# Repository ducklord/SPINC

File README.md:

# SPINC - DIY Automatic Battery Charger

## Overview

SPINC is an Open-Source NiMH charging station that can automatically load and eject AA battery cells. Simply drop batteries into the top of the device, regardless of their polarity. The internal mechanism picks up one cell at a time and fast-charges them sequentially. Up to 7 fully charged batteries can be conveniently stored inside the device for easy access. In addition, SPINC doubles as a desk clock, displaying the date and time on its high-resolution LCD.

<div align="center">
  
</div>

### Features
* Fast-charges AA NiMH cells at up to 1A
* Automatic cell loading and ejection
* Electronic polarity-correction
* Voltage, temperature and charge time monitoring
* 240x400px monochrome LCD
* Date and time display using LVGL interface
* Compact and fully 3D-printed

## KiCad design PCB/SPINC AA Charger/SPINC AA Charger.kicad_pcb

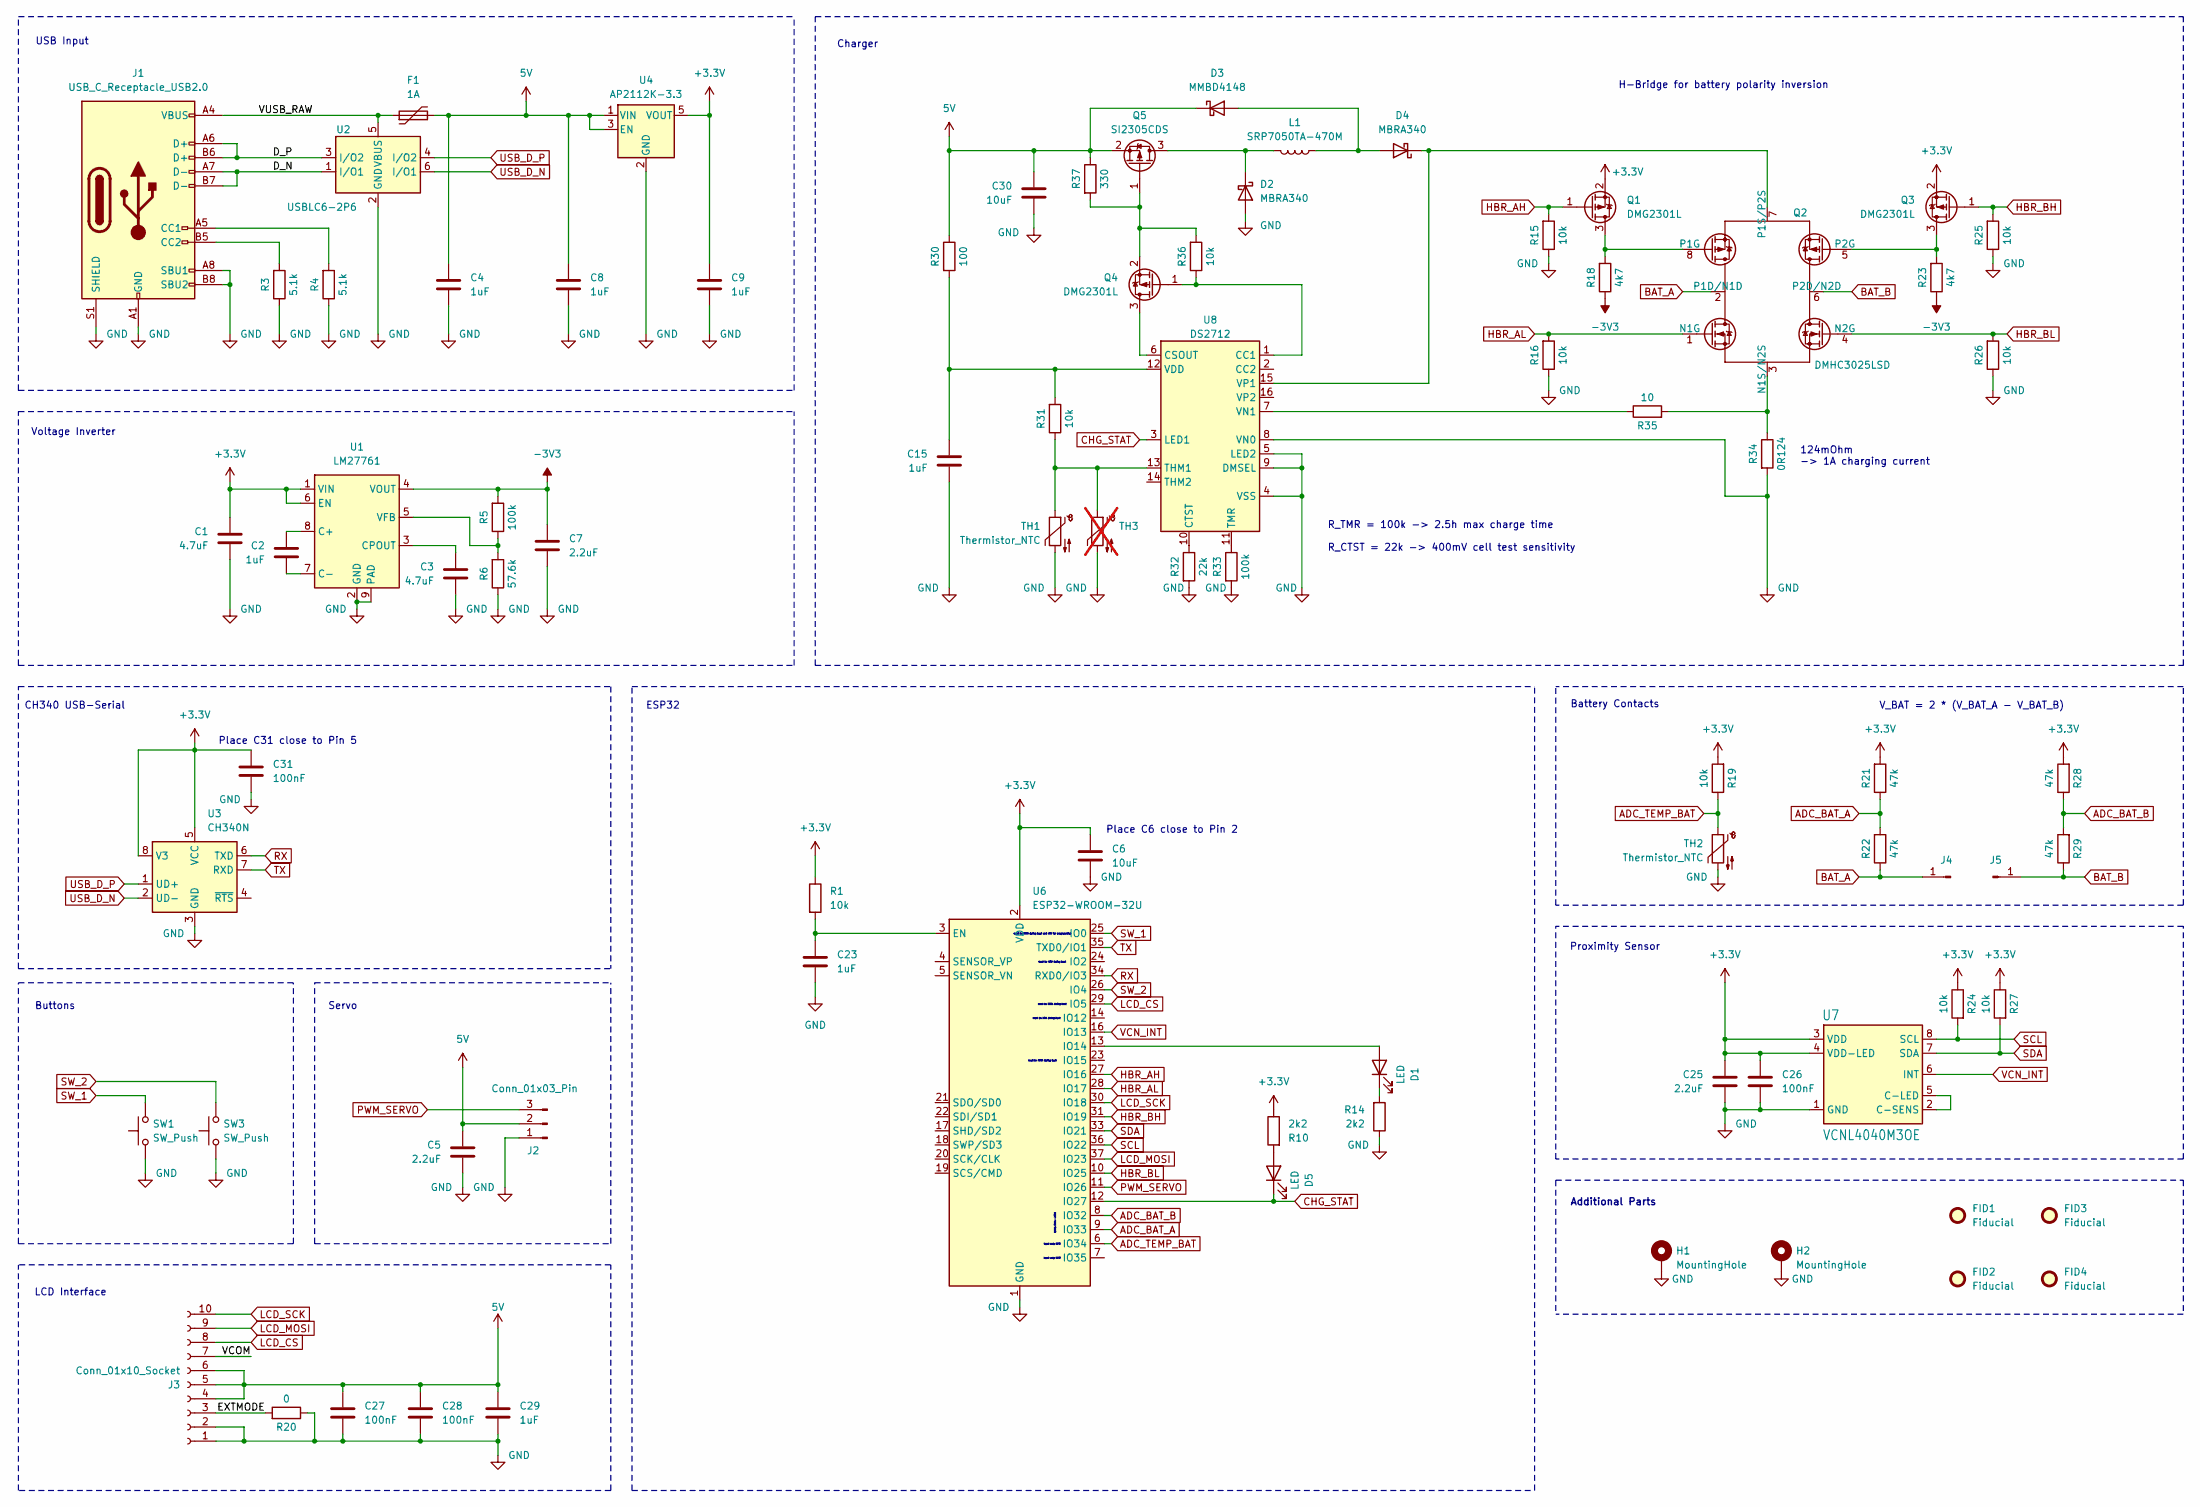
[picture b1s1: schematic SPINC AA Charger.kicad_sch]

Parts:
C1, C3: 4.7uF; C_0603_1608Metric
C2, C4, C8, C9, C15, C23, C29: 1uF; C_0603_1608Metric; LCSC C15849
C5, C7, C25: 2.2uF; C_0603_1608Metric
C6, C30: 10uF; C_0603_1608Metric
C26, C27, C28, C31: 100nF; C_0603_1608Metric
D1, D5: LED; LED_0603_1608Metric; LCSC C965807
D2, D4: MBRA340; D_SMA
D3: MMBD4148; TSOT-23
F1: 1A; Fuse_1206_3216Metric_Pad1.42x1.75mm_HandSolder
FID1, FID2, FID3, FID4: Fiducial; Fiducial_1mm_Mask2mm
H1, H2: MountingHole; MountingHole_3.2mm_M3_Pad_Via
J1: USB_C_Receptacle_USB2.0; USB_C_Receptacle_HRO_TYPE-C-31-M-12; LCSC C2982555
J2: Conn_01x03_Pin; PinHeader_1x03_P2.54mm_Vertical; LCSC C722693
J3: Conn_01x10_Socket; 68711014022; LCSC C2919540
J4, J5: Conn_01x01_Pin; BatteryHolder_Keystone_590; LCSC C3029553
L1: SRP7050TA-470M; L_Bourns_SRP7050TA_7.3x6.6mm
Q1, Q3: DMG2301L; SOT-23; LCSC C102619
Q2: DMHC3025LSD; SO-8_3.9x4.9mm_P1.27mm; LCSC C156387
Q4: DMG2301L; SOT-23
Q5: SI2305CDS; SOT-23
R1, R15, R16, R19, R24, R25, R26, R27, R31, R36: 10k; R_0603_1608Metric
R3, R4: 5.1k; R_0603_1608Metric; LCSC C23186
R5, R33: 100k; R_0603_1608Metric
R6: 57.6k; R_0603_1608Metric; LCSC C170635
R10, R14: 2k2; R_0603_1608Metric; LCSC C4190
R18, R23: 4k7; R_0603_1608Metric
R20: 0; R_0603_1608Metric
R21, R22, R28, R29: 47k; R_0603_1608Metric
R30: 100; R_0603_1608Metric
R32: 22k; R_0603_1608Metric
R34: 0R124; R_2512_6332Metric
R35: 10; R_0603_1608Metric
R37: 330; R_0603_1608Metric
SW1, SW3: SW_Push; Panasonic_EVQPUM_EVQPUD; LCSC C388642
TH1, TH2: Thermistor_NTC; R_0603_1608Metric; LCSC C13564
TH3: Thermistor_NTC; R_LDR_4.9x4.2mm_P2.54mm_Vertical; not fitted
U1: LM27761; WSON-8-1EP_2x2mm_P0.5mm_EP0.9x1.6mm
U2: USBLC6-2P6; SOT-666; LCSC C2827693
U3: CH340N; SOP-8_3.9x4.9mm_P1.27mm
U4: AP2112K-3.3; SOT-23-5; LCSC C51118
U6: ESP32-WROOM-32U
U7: VCNL4040M3OE; VISHAY_VCNL4040_4X2X1.1; LCSC C142526
U8: DS2712; TSSOP-16_4.4x5mm_P0.65mm

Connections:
5V: C4.1, C5.1, C8.1, C27.1, C28.1, C29.1, C30.1, D3.3 (K), F1.2, J2.2, J3.4, J3.5, J3.6, Q5.2 (S), R30.1, R37.1, U4.1 (VIN), U4.3 (EN)
+3.3V: C1.1, C6.1, C9.1, C25.1, C26.1, C31.1, Q1.2 (S), Q3.2 (S), R1.1, R10.1, R19.2, R21.2, R24.1, R27.1, R28.2, U1.1 (VIN), U1.6 (EN), U3.5 (VCC), U3.8 (V3), U4.5 (VOUT), U6.2 (VDD), U7.3 (VDD), U7.4 (VDD-LED)
-3V3: C7.1, R5.2, R18.1, R23.1, U1.4 (VOUT)
/D_N: J1.A7 (D-), J1.B7 (D-), U2.1 (I/O1)
/D_P: J1.A6 (D+), J1.B6 (D+), U2.3 (I/O2)
/EXTMODE: J3.3, R20.2
/VCOM: J3.7
/VUSB_RAW: F1.1, J1.A4 (VBUS), J1.A9 (VBUS), J1.B4 (VBUS), J1.B9 (VBUS), U2.5 (VBUS)
ADC_BAT_A: R21.1, R22.2, U6.9 (IO33)
ADC_BAT_B: R28.1, R29.2, U6.8 (IO32)
ADC_TEMP_BAT: R19.1, TH2.1, U6.6 (IO34)
BAT_A: J4.1, Q2.2 (P1D/N1D), R22.1
BAT_B: J5.1, Q2.6 (P2D/N2D), R29.1
CHG_STAT: D5.1 (K), U6.12 (IO27), U8.3 (LED1)
GND: C1.2, C3.2, C4.2, C5.2, C6.2, C7.2, C8.2, C9.2, C15.2, C23.2, C25.2, C26.2, C27.2, C28.2, C29.2, C30.2, C31.2, D2.2 (A), H1.1, H2.1, J1.A1 (GND), J1.A8 (SBU1), J1.A12 (GND), J1.B1 (GND), J1.B8 (SBU2), J1.B12 (GND), J1.S1 (SHIELD), J2.1, J3.1, J3.2, R3.1, R4.1, R6.1, R14.1, R15.1, R16.1, R20.1, R25.1, R26.1, R32.2, R33.2, R34.2, SW1.1, SW3.1, TH1.2, TH2.2, TH3.2, U1.2 (GND), U1.9 (PAD), U2.2 (GND), U3.3 (GND), U4.2 (GND), U6.1 (GND), U6.15 (GND), U6.38 (GND), U6.39 (GND), U7.1 (GND), U8.4 (VSS), U8.5 (LED2), U8.8 (VN0), U8.9 (DMSEL)
HBR_AH: Q1.1 (G), R15.2, U6.27 (IO16)
HBR_AL: Q2.1 (N1G), R16.2, U6.28 (IO17)
HBR_BH: Q3.1 (G), R25.2, U6.31 (IO19)
HBR_BL: Q2.4 (N2G), R26.2, U6.10 (IO25)
LCD_CS: J3.8, U6.29 (IO5)
LCD_MOSI: J3.9, U6.37 (IO23)
LCD_SCK: J3.10, U6.30 (IO18)
unnamed: D1.2 (A), U6.13 (IO14)
unnamed: D1.1 (K), R14.2
unnamed: D2.1 (K), L1.2, Q5.3 (D)
unnamed: D3.1 (A), D4.2 (A), L1.1
unnamed: D4.1 (K), Q2.7 (P1S/P2S), U8.15 (VP1)
unnamed: D5.2 (A), R10.2
unnamed: J1.A5 (CC1), R4.2
unnamed: J1.B5 (CC2), R3.2
unnamed: Q1.3 (D), Q2.8 (P1G), R18.2
unnamed: Q2.3 (N1S/N2S), R34.1, R35.2
unnamed: Q2.5 (P2G), Q3.3 (D), R23.2
unnamed: Q4.3 (D), U8.6 (CSOUT)
unnamed: Q4.1 (G), R36.1, U8.1 (CC1)
unnamed: Q4.2 (S), Q5.1 (G), R36.2, R37.2
unnamed: C2.1, U1.8 (C+)
unnamed: C2.2, U1.7 (C-)
unnamed: C3.1, U1.3 (CPOUT)
unnamed: R5.1, R6.2, U1.5 (VFB)
unnamed: C23.1, R1.2, U6.3 (EN)
unnamed: U7.2 (C-SENS), U7.5 (C-LED)
unnamed: R32.1, U8.10 (CTST)
unnamed: R31.1, TH1.1, TH3.1, U8.13 (THM1)
unnamed: R33.1, U8.11 (TMR)
unnamed: C15.1, R30.2, R31.2, U8.12 (VDD)
unnamed: R35.1, U8.7 (VN1)
PWM_SERVO: J2.3, U6.11 (IO26)
RX: U3.6 (TXD), U6.34 (RXD0/IO3)
SCL: R24.2, U6.36 (IO22), U7.8 (SCL)
SDA: R27.2, U6.33 (IO21), U7.7 (SDA)
SW_1: SW1.2, U6.25 (IO0)
SW_2: SW3.2, U6.26 (IO4)
TX: U3.7 (RXD), U6.35 (TXD0/IO1)
USB_D_N: U2.6 (I/O1), U3.2 (UD-)
USB_D_P: U2.4 (I/O2), U3.1 (UD+)
VCN_INT: U6.16 (IO13), U7.6 (INT)

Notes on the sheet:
ESP32
ADC1: IO32--IO39
Voltage Inverter
Place C31 close to Pin 5
Buttons
must be HIGH during boot and LOW for programming
Charger
H-Bridge for battery polarity inversion
must be HIGH during boot
Battery Contacts
Input only GPIO
Additional Parts
Servo
CH340 USB-Serial
must be LOW during boot
V_BAT = 2 * (V_BAT_A - V_BAT_B)
LCD Interface
Place C6 close to Pin 2
USB Input
Proximity Sensor
124mOhm -> 1A charging current
R_TMR = 100k -> 2.5h max charge time R_CTST = 22k -> 400mV cell test sensitivity

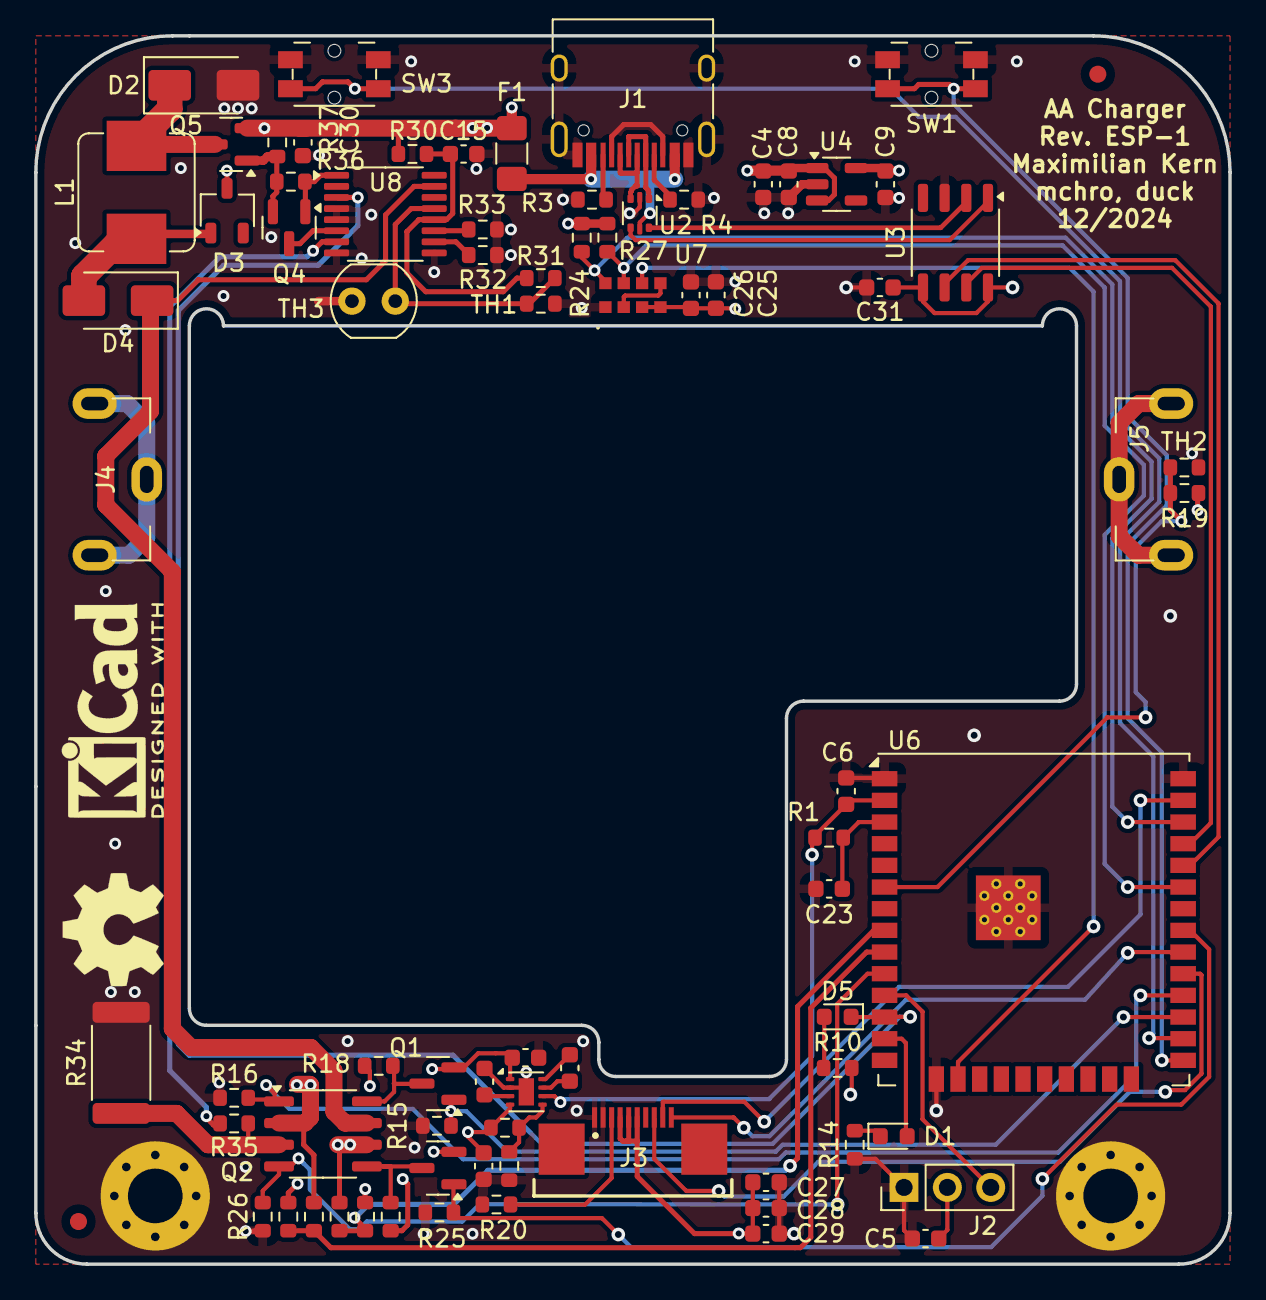
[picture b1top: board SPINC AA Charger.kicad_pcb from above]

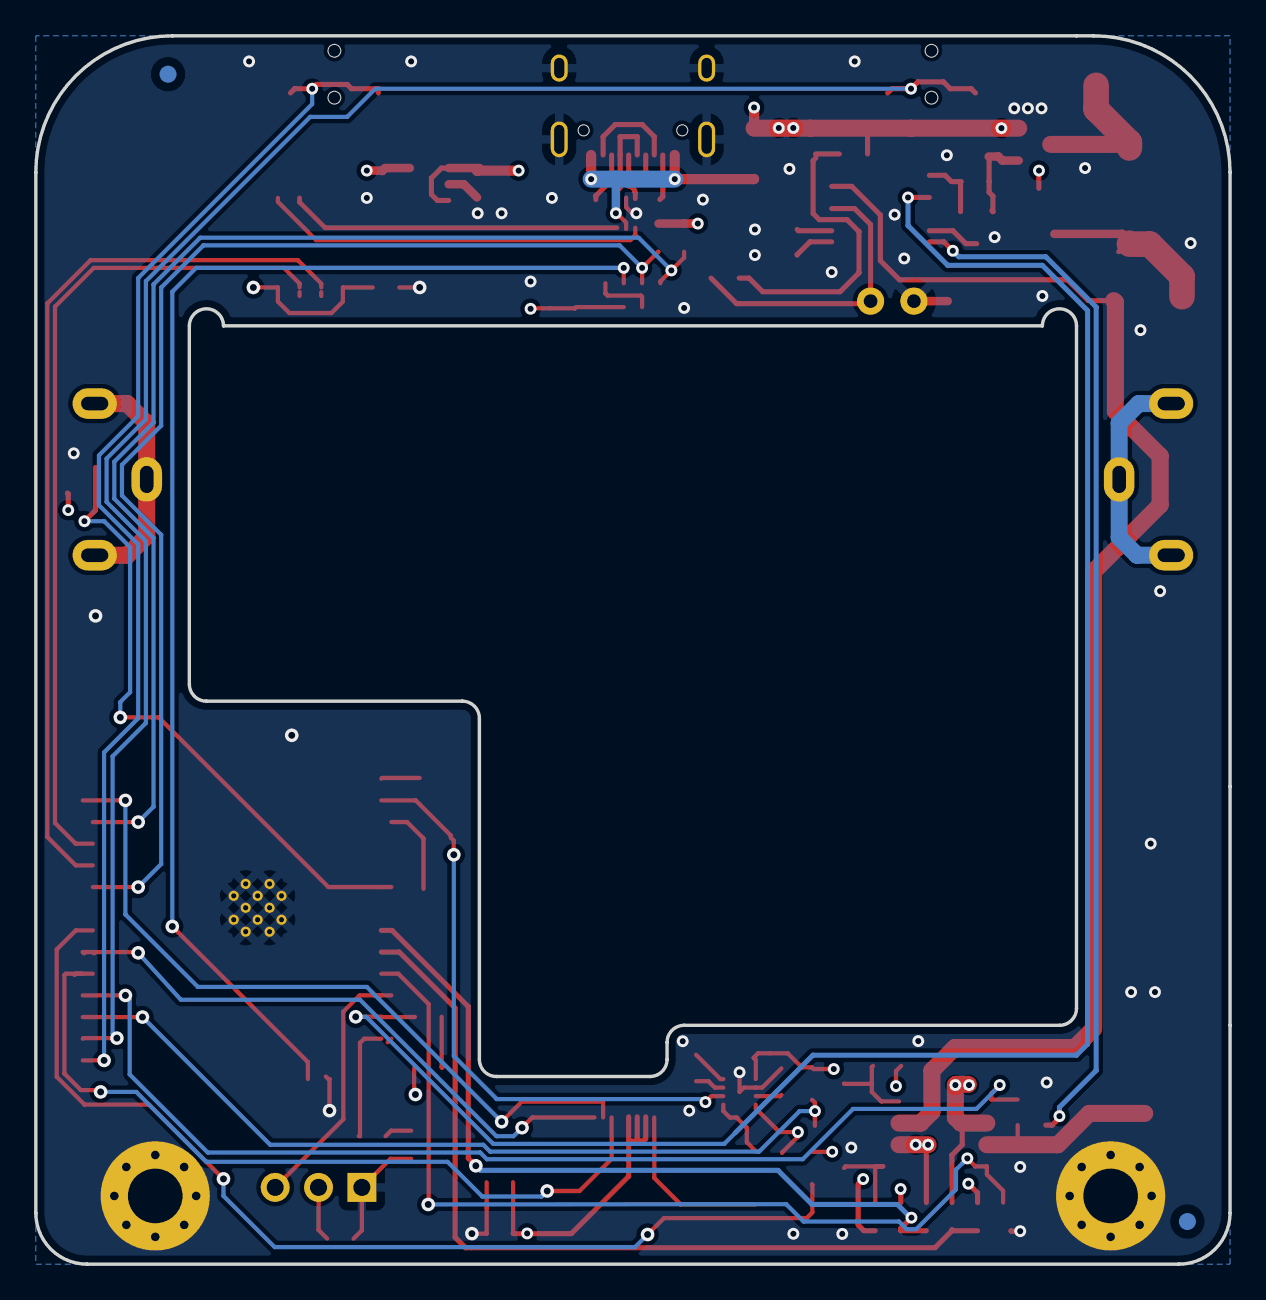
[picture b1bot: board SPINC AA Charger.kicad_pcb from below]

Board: 4 copper layers, 70.0 x 72.0 mm, 82 parts (2 on the bottom side), 56 nets.

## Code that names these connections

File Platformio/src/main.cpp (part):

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// Pin assignment -----------------------------------------------------------------------------------------------------------------------

#ifdef ARDUINO_ARCH_ESP32
  #define SW_A 4 // SW_2
  #define SW_B 0 // SW_1
  #define USER_LED 14 // 25 for Pico

  #define LCD_CS 5
  #define LCD_MOSI 23
  #define LCD_SCK 18

  #define SDA 21
  #define SCL 22
  #define VCN_INT 13

  #define CHG_STAT 27
  #define CHG_TMR 15 //NOT CONNECTED!

  #define PWM_SERVO 26

  #define HBR_AH 16
  #define HBR_AL 17
  #define HBR_BL 25
  #define HBR_BH 19

  #define ADC_BAT_A 33
  #define ADC_BAT_B 32
  #define ADC_TEMP_BAT 34

#else
  #define SW_A 2 // SW_2
  #define SW_B 0 // SW_1
  #define USER_LED 14 // 25 for Pico

  #define LCD_CS 1
  #define LCD_MOSI 3
  #define LCD_SCK 6

  #define SDA 4
  #define SCL 5
  #define VCN_INT 7

  #define CHG_STAT 8
  #define CHG_TMR 11

  #define PWM_SERVO 15

  #define HBR_AH 9
  #define HBR_AL 10
  #define HBR_BL 12
  #define HBR_BH 13

  #define ADC_BAT_A A0
  #define ADC_BAT_B A1
  #define ADC_TEMP_BAT A3
#endif

// H-bridge declarations
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  pinMode(SW_A, INPUT_PULLUP);

  // Proximity Sensor Interrupt
  pinMode(VCN_INT, INPUT);

  // H-Bridge Controls
  pinMode(HBR_AL, OUTPUT);
  pinMode(HBR_AH, OUTPUT);
  pinMode(HBR_BL, OUTPUT);
  pinMode(HBR_BH, OUTPUT);
  pinMode(ADC_BAT_A, INPUT);
  pinMode(ADC_BAT_B, INPUT);
  pinMode(ADC_TEMP_BAT, INPUT);

  // Charger
  pinMode(CHG_STAT, INPUT_PULLUP);
  pinMode(CHG_TMR, INPUT);
  
  // Servo
  pinMode(PWM_SERVO, OUTPUT);

  //LCD
  pinMode(LCD_CS, OUTPUT); // this line is important since the adafruit library was ported to HW SPI!

  // Serial Init
  Serial.begin(115200);
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
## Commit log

2024-11-08 Initial Upload
2024-11-22 Small fixes for the PCB
    - Changed fuse from 500mA to 1A (when charging at full 1A, the device draws slightly more than 500mA)
    - Changed R32 from 80k to 22k (somehow the cell check fails with 100mV sensitivity)
2024-11-23 Fixed Readme
2024-12-03 Added fabrication files
    - Please double-check the files before odering anything!
    - The BOM does not include JLCPCB numbers yet.
2024-12-12 Add ESP32-WROOM-32U and CH340 instead of RP2040
2024-12-12 WIP: initial pcb placement
2024-12-13 Route everything
2024-12-14 Optimize a little routing
2024-12-14 Make the GND pads of the ESP32 0.3mm, much cheaper to manufacture
2024-12-14 Fix a few routing warnings
2024-12-14 Optimize PCB some more around ESP32
2024-12-14 Re-arrange a bit and reduce the number of vias.
2024-12-15 Fabrication details
2024-12-15 Fixup a few PCB warnings, give credit
2024-12-17 Fix 3V3 supply for CH340; move capacitor to supply pin
2024-12-27 Initial port for ESP32 - compiles
2024-12-27 Move the modified "Adafruit SHARP Memory Display" to a different location
    So it can be included only on the pico environment.
2025-01-05 Connect to NTP to setup local time.
2025-01-05 Updated magic servo positions to fit current model.
2025-01-12 Modified arm to give room for the ESP32.
2025-01-12 Updated servo hole size to be able to fit a SG90.
